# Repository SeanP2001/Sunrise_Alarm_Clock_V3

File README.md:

# Sunrise Alarm Clock V3

**Table of Contents**

- [Introduction](#introduction)
- [Brief](#brief)
- [Development Roadmap](#development-roadmap)
- [Circuitry](#circuitry)
  - [Schematics](#schematics)
    - [Main PCB](#main-pcb)
    - [Button PCB](#button-pcb)
    - [Light PCB](#light-pcb)
  - [PCB Design](#pcb-design)
    - [Main PCB](#main-pcb-1)
    - [Button PCB](#button-pcb-1)
    - [Light PCB](#light-pcb-1)
  - [Soldering](#soldering)
    - [Main PCB](#main-pcb-2)
    - [Button PCB](#button-pcb-2)
    - [Light PCB](#light-pcb-2)
- [Enclosure](#enclosure)
  - [CAD Enclosure](#cad-enclosure)
  - [Assembled Enclosure](#assembled-enclosure)
- [Code](#code)
  - [Documentation](#documentation)
  - [How to Add a New App](#how-to-add-a-new-app)
- [Further Work](#further-work)

## Introduction

This is the third version of the "Sunrise Alarm Clock" project. [The first version](https://github.com/SeanP2001/Arduino_Sunrise_Alarm_Clock) used an Arduino Mega and an LCD keypad shield. [The second version](https://github.com/SeanP2001/Sunrise_Alarm_Clock_V2) used a Wemos D1 mini (ESP8266) and 0.96" OLED on a single custom PCB. This design was fully functional but it did not look like an alarm clock. I started version 3 with the aim of making the alarm look more premium. 

<div style="display: flex; justify-content: space-between;">

</div>
<p align="center"><i>Alarm V1, Alarm V2 and Alarm V3 Concept</i></p>

This project was sponsored by PCBWay. To order high-quality, custom PCBs go to [PCBWay.com](https://www.pcbway.com/)

## Brief

The alarm needed to:
- Tell the time
- Use a real-time clock (RTC) to keep the time 
- Use an NTP server to update the time periodically
- Include a larger, 1.5" OLED 
- Include three capacitive touch buttons
- Include two timed USB ports
- Include a bright ringlight on the clock face
- Include a buzzer
- Have a premium feel

## Development Roadmap

The following roadmap outlines the planned milestones for the project. Each step includes testing and documenting.

| **Version**   | **Description**                                            |
|---------------|------------------------------------------------------------|
| V3.1-alpha    | Capture Schematic                                          |
| V3.2-alpha    | Design Main PCB                                            |
| V3.3-alpha    | Design Light PCB                                           |
| V3.4-alpha    | Design Button PCB                                          |
| V3.5-alpha    | Design and Fabricate Enclosure                             |
| V3.6-alpha    | Solder and Assemble                                        |
| V3.7-alpha    | Test Hardware and Document                                 |
| V3.8-alpha    | Program Inputs and Outputs                                 |
| V3.9-alpha    | Implement App Infrastructure                               |
| V3.10-alpha   | Develop Alarm App                                          |
| V3.11-alpha   | Develop Light App                                          |
| V3.12-alpha   | Develop USB App                                            |
| V3.13-alpha   | Develop Settings App                                       |
| V3.14-alpha   | Implement WiFi, NTP Time Sync and Settings Portal          |
| V3.0-release  | Initial Release (Document, Test and Fix Bugs)              |

## Circuitry

### Schematics

#### Main PCB

#### Button PCB

#### Light PCB

### PCB Design

#### Main PCB

<div style="display: flex; justify-content: space-between;">

</div>
<p align="center"><i>Main PCB Front and Back</i></p>

#### Button PCB

<div style="display: flex; justify-content: space-between;">

</div>
<p align="center"><i>Button PCB Front and Back</i></p>

#### Light PCB

<div style="display: flex; justify-content: space-between;">

</div>
<p align="center"><i>Light PCB Front and Back</i></p>

### Soldering

I was really impressed by the quality of the PCBs sent by PCBWay. To order high-quality, custom PCBs go to [PCBWay.com](https://www.pcbway.com/). 

#### Main PCB

<div style="display: flex; justify-content: space-between;">

</div>
<p align="center"><i>Main PCB Front and Back</i></p>

<p align="center"><i>Main PCB Soldered</i></p>

#### Button PCB

<div style="display: flex; justify-content: space-between;">

</div>
<p align="center"><i>Button PCB Front and Back</i></p>

<p align="center"><i>Button PCB Soldered</i></p>

#### Light PCB

<div style="display: flex; justify-content: space-between;">

</div>
<p align="center"><i>Light PCB Front and Back</i></p>

<p align="center"><i>Light PCB Soldered</i></p>

## Enclosure

### CAD Enclosure

<div style="display: flex; justify-content: space-between;">

</div>
<div style="display: flex; justify-content: space-between; margin-top: 10px;">

</div>

### Assembled Enclosure

<div style="display: flex; justify-content: center;">

</div>
<div style="display: flex; justify-content: center;">

</div>

## Code

### Documentation

View the Doxygen documentation for this project [here](https://raw.githack.com/SeanP2001/Sunrise_Alarm_Clock_V3/main/Code/Documentation/html/index.html).

### How to Add a New App

1. Copy the `TemplateApp.h` and `TemplateApp.cpp` files, changing their names to reflect your app.  
2. Change the header guards, file headers and and include statements to the new file names.  
3. Do a find and replace for the phrase "TemplateApp" replacing it with the name of your app (both files).  
4. Add code to each of the functions.  
5. Include the header file in the main program.  
6. Instantiate the new `____App` object.  
7. Increment the `noOfApps` variable.  
8. Add a reference to the new app object at the next index of the `apps` array. e.g.`apps[i] = &____App;`.

## Further Work

In future I would like to;
- Change the design to not use vinyl as it is difficult to get a perfect result using it.
- Add software functions:
  - Wake up games
  - Daily weather forecast
  - Daily calendar events
  - Log sleep and wake times
  - Mood tracker
  - Habit tracker

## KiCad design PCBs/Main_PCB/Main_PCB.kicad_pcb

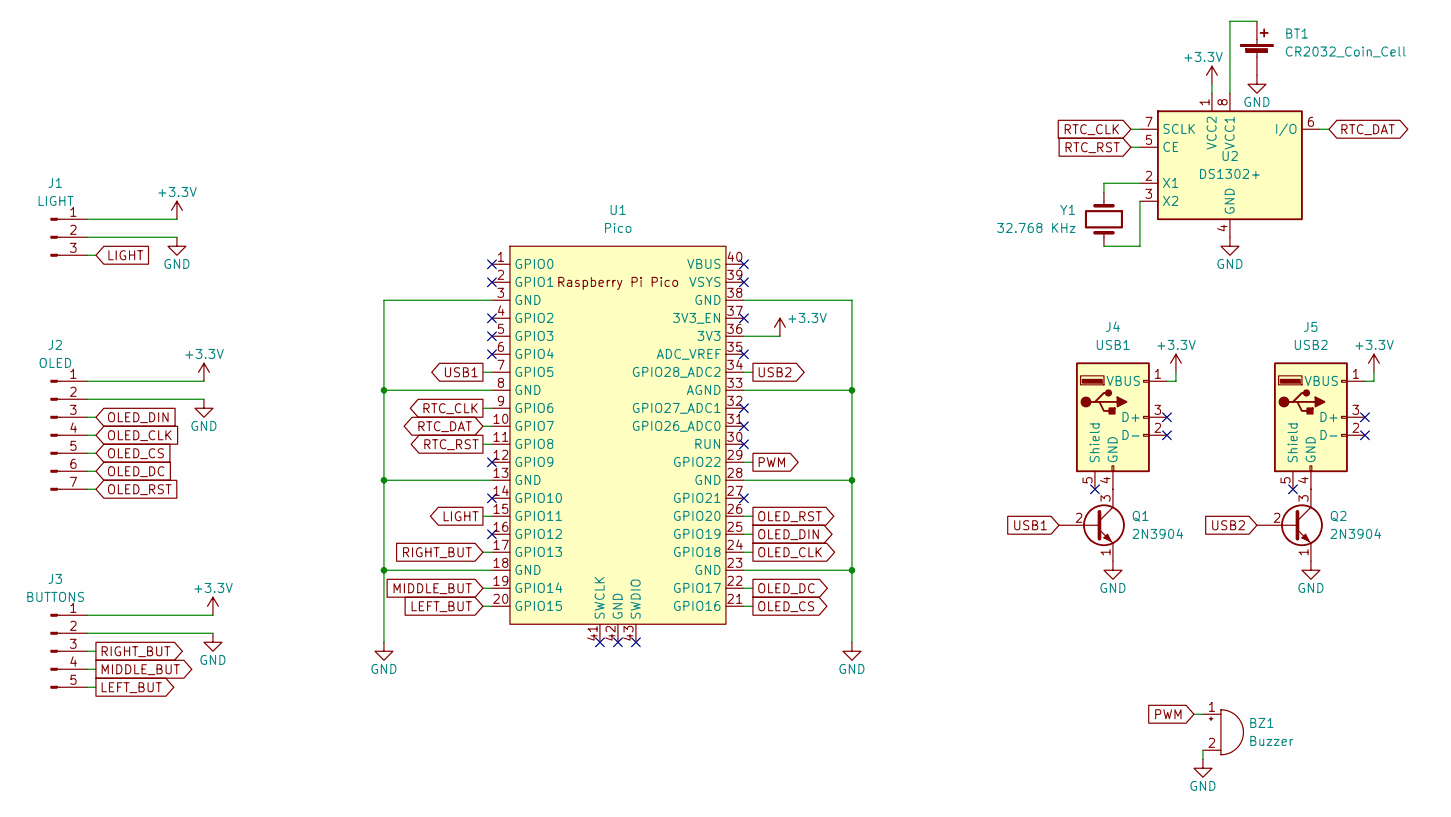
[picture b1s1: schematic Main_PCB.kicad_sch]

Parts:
BT1: CR2032_Coin_Cell; Vertical_CR2032_Battery_Holder
BZ1: Buzzer; MagneticBuzzer_ProSignal_ABT-410-RC
J1: LIGHT; PinHeader_1x03_P2.54mm_Vertical
J2: OLED; PinHeader_1x07_P2.54mm_Vertical
J3: BUTTONS; PinHeader_1x05_P2.54mm_Vertical
J4: USB1; USB_A_CONNFLY_DS1095-WNR0
J5: USB2; USB_A_CONNFLY_DS1095-WNR0
Q1, Q2: 2N3904; TO-92_Inline
U1: Pico; RPi_Pico_SMD_TH
U2: DS1302+; DIP-8_W7.62mm
Y1: 32.768 KHz; Crystal_DS26_D2.0mm_L6.0mm_Horizontal

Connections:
+3.3V: J1.1, J2.1, J3.1, J4.1 (VBUS), J5.1 (VBUS), U1.36 (3V3), U2.1 (VCC2)
GND: BT1.2 (-), BZ1.2 (+), J1.2, J2.2, J3.2, Q1.1 (E), Q2.1 (E), U1.3 (GND), U1.8 (GND), U1.13 (GND), U1.18 (GND), U1.23 (GND), U1.28 (GND), U1.33 (AGND), U1.38 (GND), U2.4 (GND)
LEFT_BUT: J3.5, U1.20 (GPIO15)
LIGHT: J1.3, U1.15 (GPIO11)
MIDDLE_BUT: J3.4, U1.19 (GPIO14)
unnamed: BT1.1 (+), U2.8 (VCC1)
unnamed: J4.4 (GND), Q1.3 (C)
unnamed: J5.4 (GND), Q2.3 (C)
unnamed: U2.2 (X1), Y1.1
unnamed: U2.3 (X2), Y1.2
OLED_CLK: J2.4, U1.24 (GPIO18)
OLED_CS: J2.5, U1.21 (GPIO16)
OLED_DC: J2.6, U1.22 (GPIO17)
OLED_DIN: J2.3, U1.25 (GPIO19)
OLED_RST: J2.7, U1.26 (GPIO20)
PWM: BZ1.1 (-), U1.29 (GPIO22)
RIGHT_BUT: J3.3, U1.17 (GPIO13)
RTC_CLK: U1.9 (GPIO6), U2.7 (SCLK)
RTC_DAT: U1.10 (GPIO7), U2.6 (I/O)
RTC_RST: U1.11 (GPIO8), U2.5 (CE)
USB1: Q1.2 (B), U1.7 (GPIO5)
USB2: Q2.2 (B), U1.34 (GPIO28_ADC2)

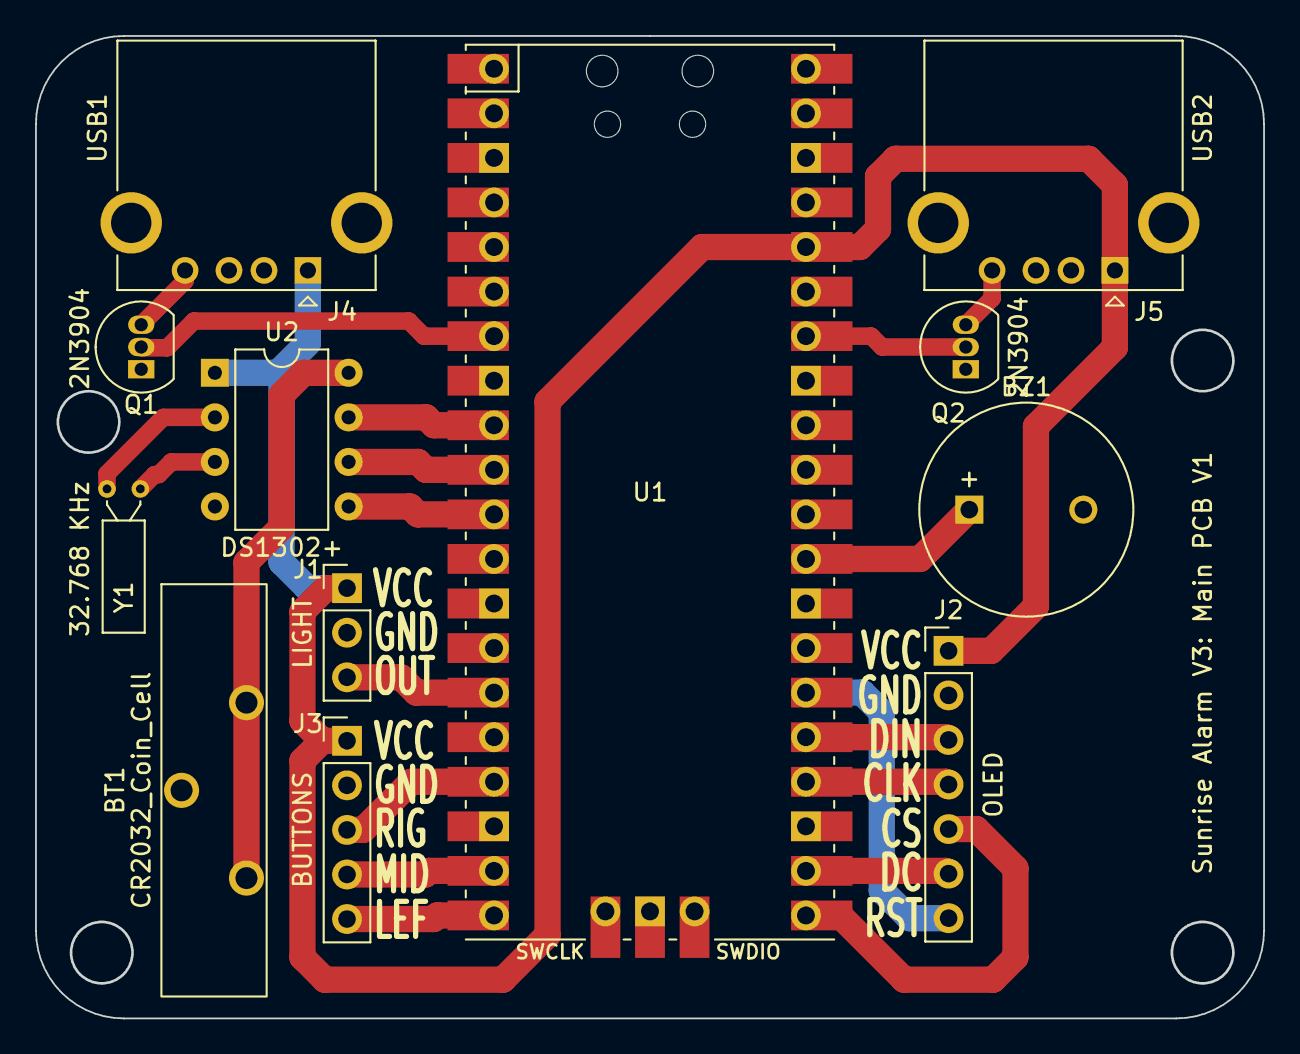
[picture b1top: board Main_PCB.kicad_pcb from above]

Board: 2 copper layers, 70.0 x 55.9 mm, 12 parts (0 on the bottom side), 22 nets.

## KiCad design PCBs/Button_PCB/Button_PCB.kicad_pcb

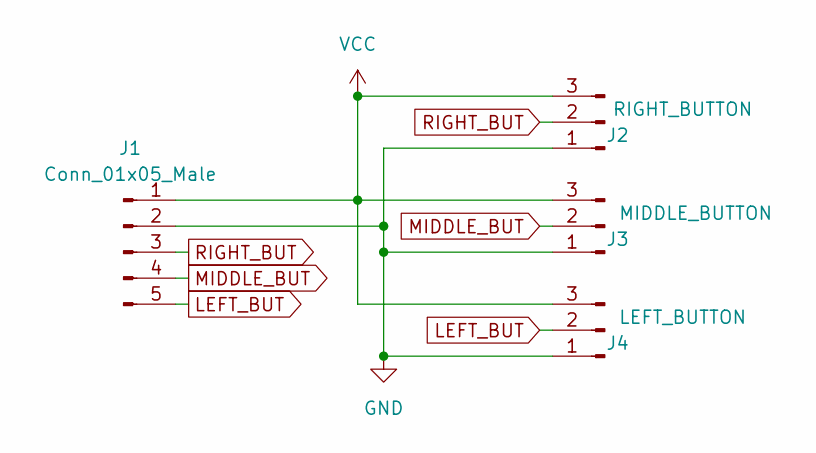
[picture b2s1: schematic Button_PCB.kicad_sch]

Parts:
J1: Conn_01x05_Male; PinHeader_1x05_P2.54mm_Vertical
J2: RIGHT_BUTTON; TTP223
J3: MIDDLE_BUTTON; TTP223
J4: LEFT_BUTTON; TTP223

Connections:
GND: J1.2, J2.1, J3.1, J4.1
LEFT_BUT: J1.5, J4.2
MIDDLE_BUT: J1.4, J3.2
RIGHT_BUT: J1.3, J2.2
VCC: J1.1, J2.3, J3.3, J4.3

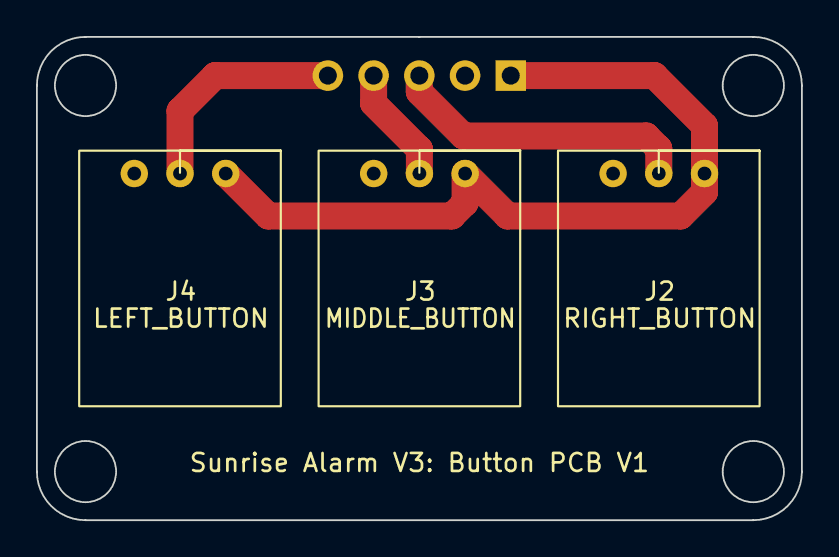
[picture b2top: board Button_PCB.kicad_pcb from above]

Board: 2 copper layers, 42.5 x 26.8 mm, 4 parts (1 on the bottom side), 5 nets.

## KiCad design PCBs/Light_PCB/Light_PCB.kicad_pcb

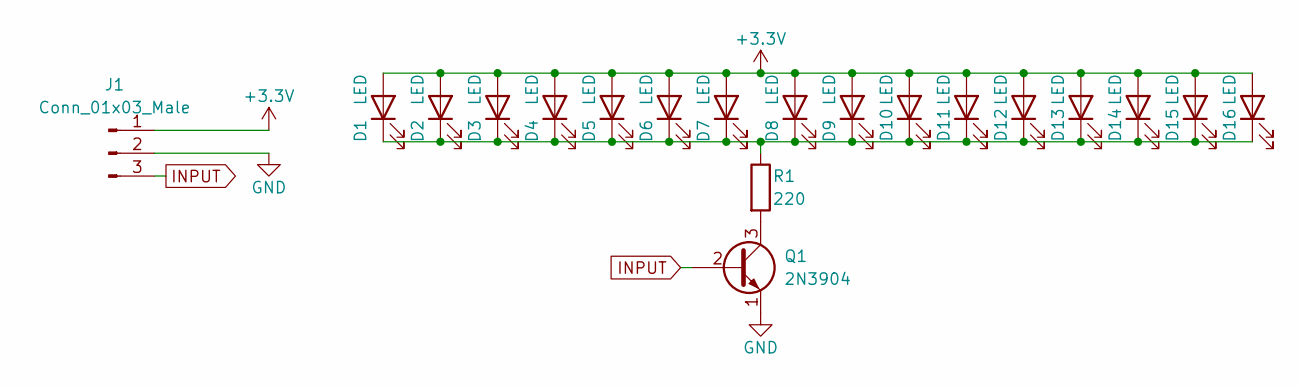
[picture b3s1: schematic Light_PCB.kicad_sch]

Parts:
D1, D2, D3, D4, D5, D6, D7, D8, D9, D10, D11, D12, D13, D14, D15, D16: LED; LED_0805_2012Metric_Pad1.15x1.40mm_HandSolder
J1: Conn_01x03_Male; PinSocket_1x03_P2.54mm_Vertical
Q1: 2N3904; TO-92_Inline
R1: 220; R_0805_2012Metric_Pad1.20x1.40mm_HandSolder

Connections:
+3.3V: D1.2 (A), D2.2 (A), D3.2 (A), D4.2 (A), D5.2 (A), D6.2 (A), D7.2 (A), D8.2 (A), D9.2 (A), D10.2 (A), D11.2 (A), D12.2 (A), D13.2 (A), D14.2 (A), D15.2 (A), D16.2 (A), J1.1
GND: J1.2, Q1.1 (E)
INPUT: J1.3, Q1.2 (B)
unnamed: D1.1 (K), D2.1 (K), D3.1 (K), D4.1 (K), D5.1 (K), D6.1 (K), D7.1 (K), D8.1 (K), D9.1 (K), D10.1 (K), D11.1 (K), D12.1 (K), D13.1 (K), D14.1 (K), D15.1 (K), D16.1 (K), R1.1
unnamed: Q1.3 (C), R1.2

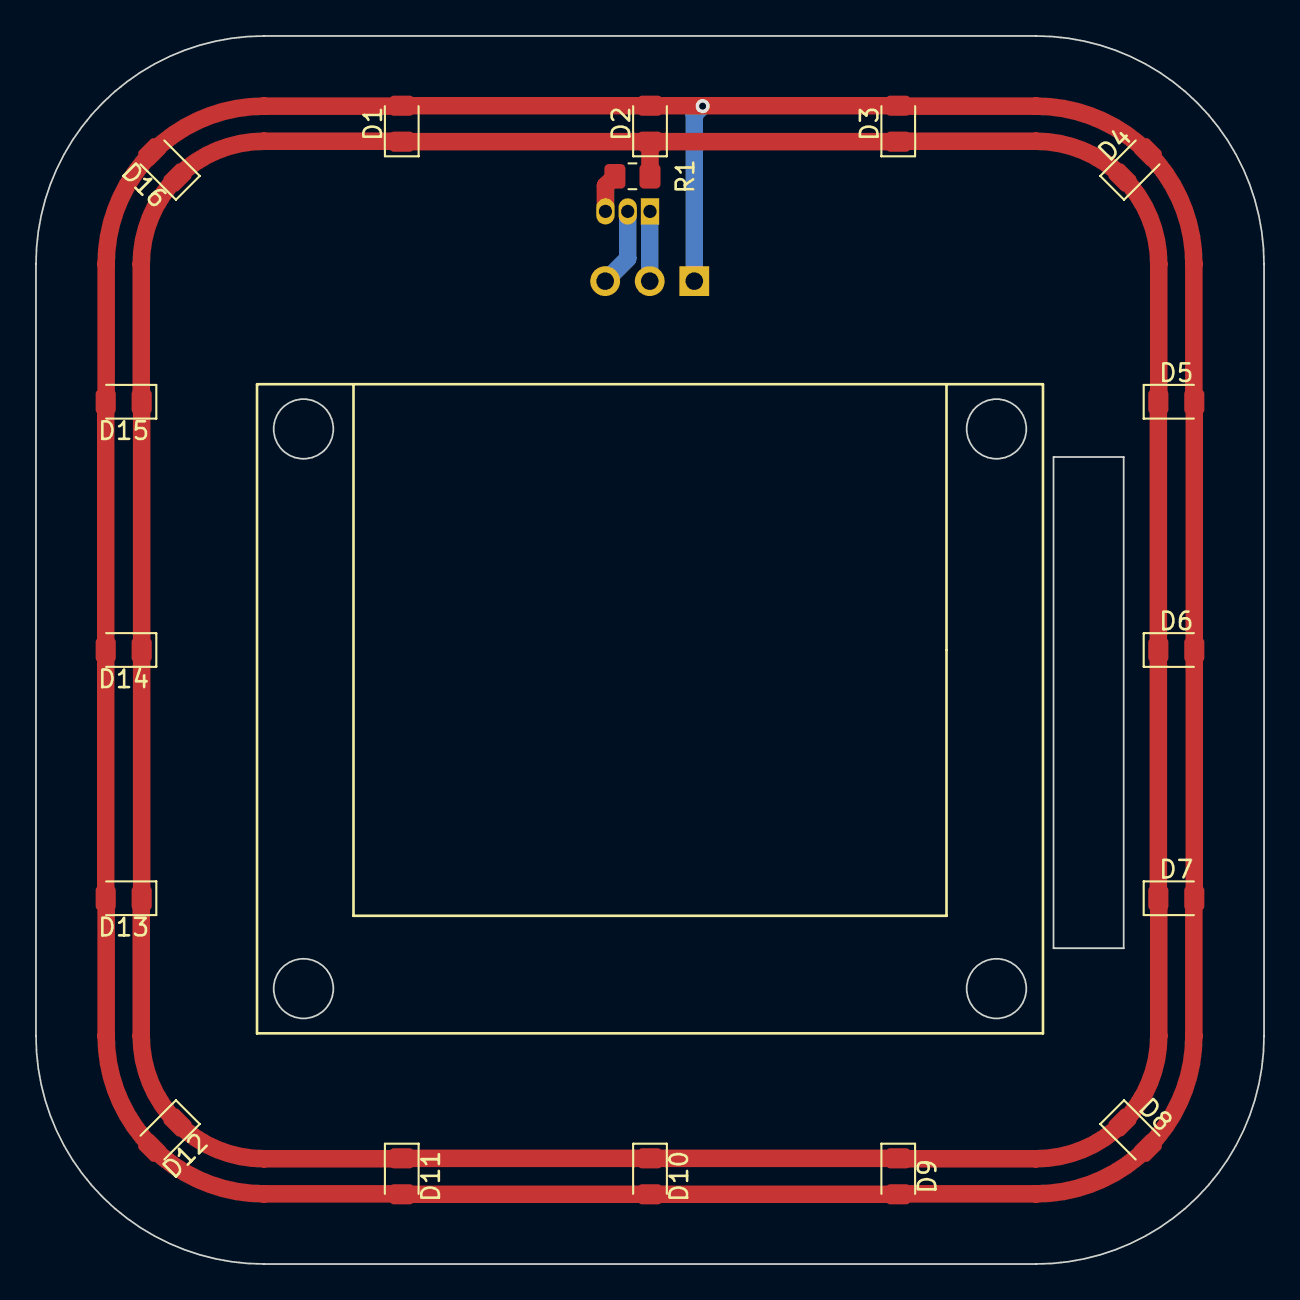
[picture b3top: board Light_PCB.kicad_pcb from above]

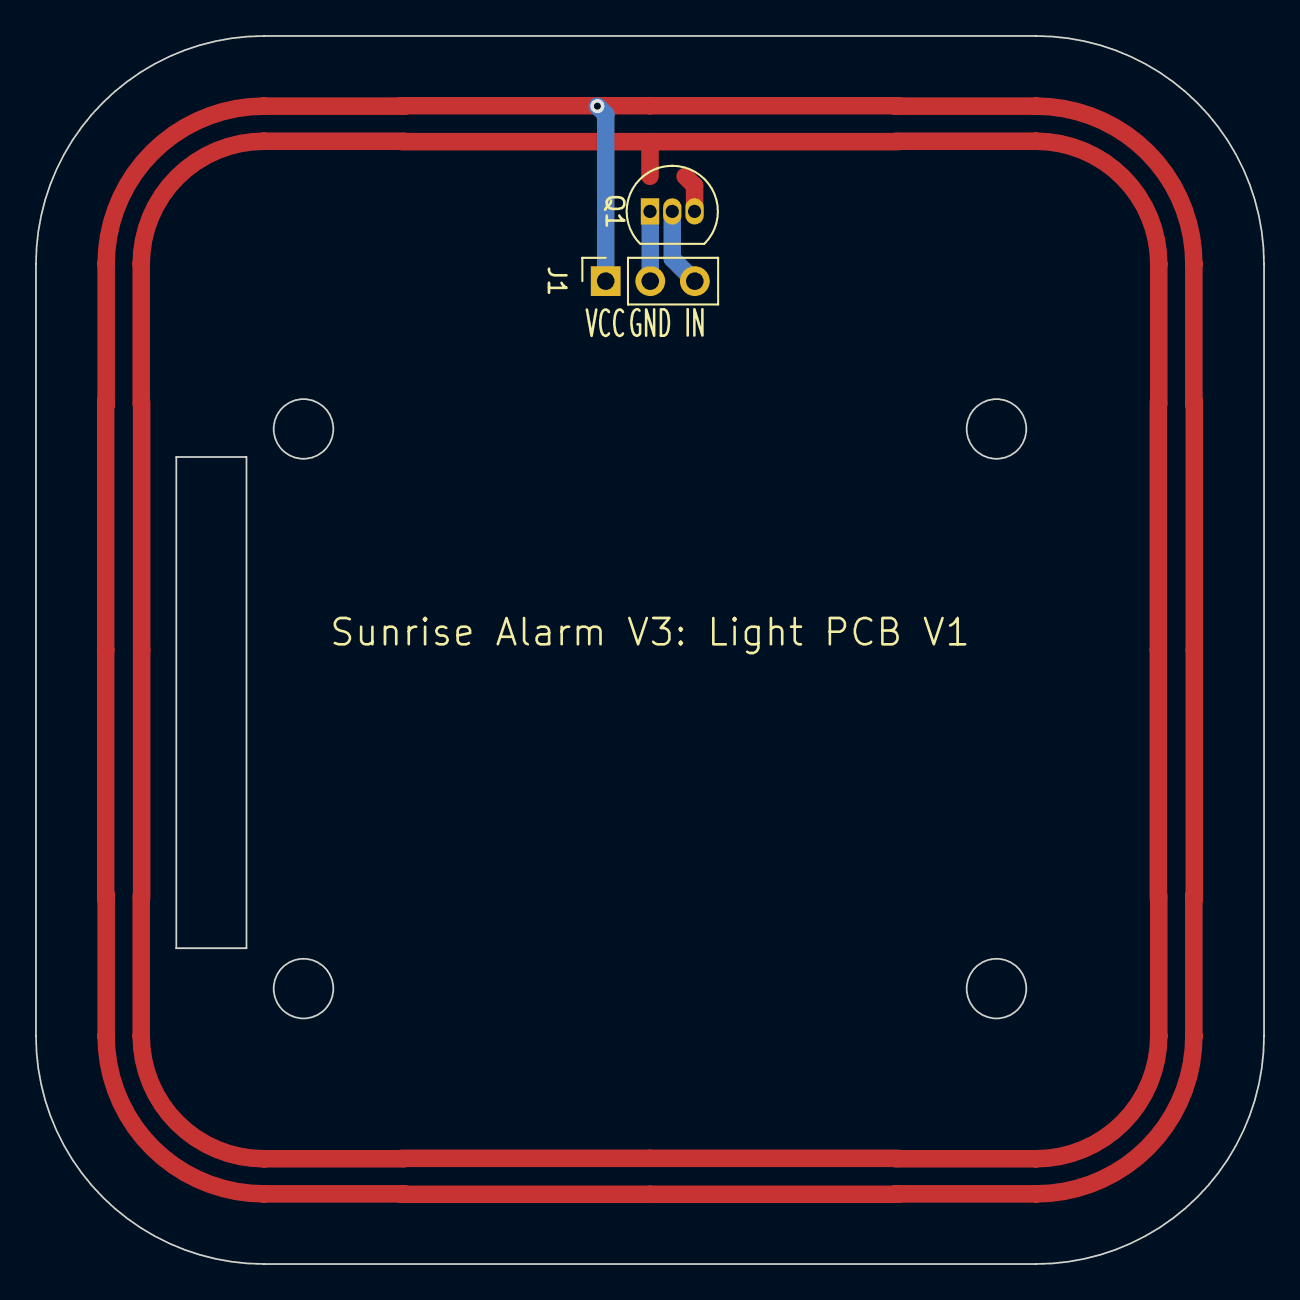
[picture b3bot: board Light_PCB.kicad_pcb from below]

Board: 2 copper layers, 70.0 x 70.0 mm, 19 parts (2 on the bottom side), 5 nets.

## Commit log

2023-09-08 V3.1.0-alpha Captured Main PCB Schematic
2023-09-08 V3.2.0-alpha Designed Main PCB
2023-09-08 V3.3.0-alpha Designed Light PCB
2023-09-08 V3.4.0-alpha Designed Button PCB
2023-09-09 V3.4.1-alpha Added PCB Labels
2023-09-23 V3.4.2-alpha Changed Buzzer Footprint
2023-10-09 V3.4.3-alpha Generated PCB Gerber Files
2023-10-15 V3.5.0-alpha Designed Enclosure
2023-11-10 V3.5.1-alpha Manufactured Enclosure
2023-11-10 V3.6.0-alpha Soldered PCBs
2023-11-10 V3.7.0-alpha Wrote Hardware Test Code
2023-11-10 V3.7.1-alpha Updated README.md
2023-11-10 V3.7.2-alpha Updated README.md
2024-01-13 V3.8.0-alpha Started Writing the SunriseAlarm Code
    - Set up interrupts for the three navigation buttons
    - Defined and implemented the Device class
    - Defined and implemented the Buzzer class
    - Started Doxygen documentation
2024-01-14 V3.9.0-alpha Implemented Basic Light Application - Defined the Hardware struct to allow direct hardware access within functions - Defined the App abstract base class - Defined and implemented the Lig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
2024-01-14 V3.10.0-alpha Implemented Basic Alarm Application - Changed App function names (backgroundFunctions -> backgroundTasks) and (displayMenuIcon -> displayMenuPage) - Defined and implemented the AlarmApp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
2024-01-14 V3.10.1-alpha Updated AlarmApp to Display the Time
2024-01-14 V3.10.2-alpha Implemented AlarmApp backgroundTasks - Added backgroundTasks code to sound the alarm if it is due to go off - Added "Development Roadmap" section to README.md - Updated "Further Work" s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
2024-01-20 V3.11.0-alpha Added Light Icons
2024-01-21 V3.11.1-alpha Implemented Light Dimming - Defined and implemented the PWMDevice class to add PWM functionality to the Device class. - Changed the light to be a PWMDevice rather than a Device. - Added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
2024-02-11 V3.11.2-alpha Implemented LightApp backgroundTasks - Added maxLevel to the PWMDevice constructor. - Added the PWMDevice::getLevel() function. - Added the PWMDevice::turnOnFull() function. - Implement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
2024-02-11 V3.12.0-alpha Added USB Icons
2024-02-11 V3.12.1-alpha Added the TemplateApp
2024-02-11 V3.12.2-alpha Implemented the USBApp
2024-02-25 V3.12.3-alpha Allowed Any Button to Turn Alarm Off
2024-02-25 V3.12.4-alpha Added Screen Timeout
